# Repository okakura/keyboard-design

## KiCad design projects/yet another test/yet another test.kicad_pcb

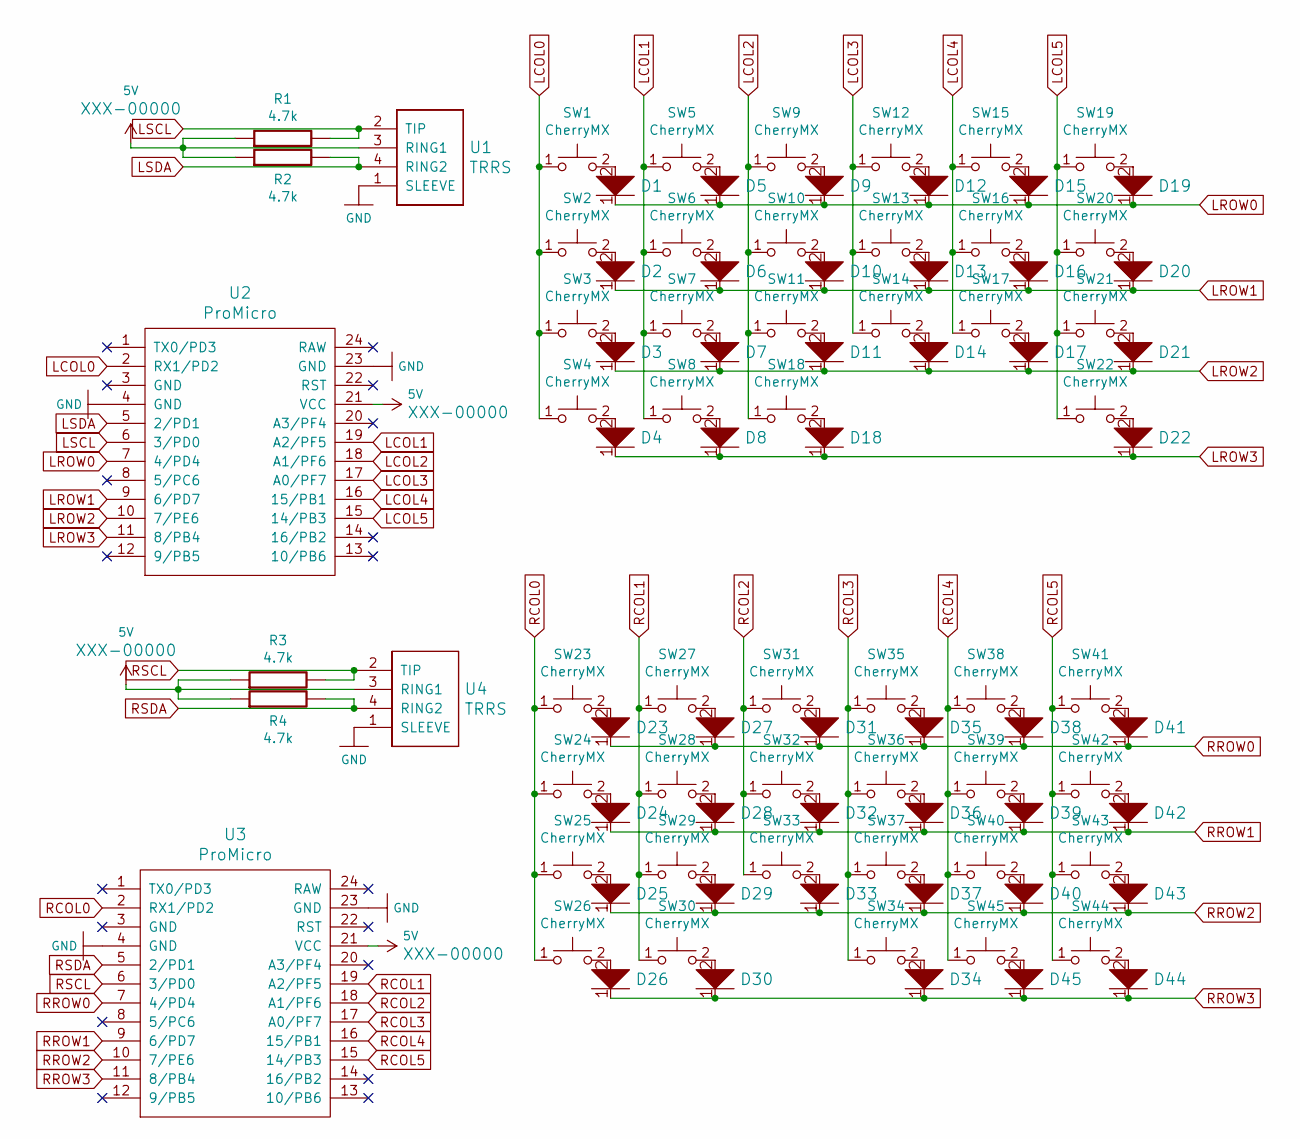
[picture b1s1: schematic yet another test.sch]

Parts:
D1, D2, D3, D4, D5, D6, D7, D8, D9, D10, D11, D12, D13, D14, D15, D16, D17, D18, D19, D20, D21, D22, D23, D24, D25, D26, D27, D28, D29, D30, D31, D32, D33, D34, D35, D36, D37, D38, D39, D40, D41, D42, D43, D44, D45: D; Diode
R1, R2, R3, R4: 4.7k; Resistor
SW1, SW5, SW6, SW7, SW9, SW10, SW11, SW12, SW13, SW14, SW15, SW16, SW17, SW19, SW20, SW21, SW23, SW24, SW25, SW27, SW28, SW29, SW31, SW32, SW33, SW34, SW35, SW36, SW37, SW38, SW39, SW40, SW43, SW44, SW45: CherryMX; CherryMX_1.00u_PCB
SW2, SW4, SW18: CherryMX; CherryMX_1.25u_PCB
SW3, SW41: CherryMX; CherryMX_1.75u_PCB
SW8, SW30, SW42: CherryMX; CherryMX_1.50u_PCB
SW22: CherryMX; CherryMX_2.25u_PCB_StabWireBottom
SW26: CherryMX; CherryMX_2.00u_PCB_StabWireBottom
U1, U4: TRRS; TRRS-PJ-320D
U2, U3: ProMicro; ArduinoProMicro

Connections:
5V: R1.1, R2.1, R3.1, R4.1, U1.3 (RING1), U2.21 (VCC), U3.21 (VCC), U4.3 (RING1)
GND: U1.1 (SLEEVE), U2.4 (GND), U2.23 (GND), U3.4 (GND), U3.23 (GND), U4.1 (SLEEVE)
LCOL0: SW1.1, SW2.1, SW3.1, SW4.1, U2.2 (RX1/PD2)
LCOL1: SW5.1, SW6.1, SW7.1, SW8.1, U2.19 (A2/PF5)
LCOL2: SW9.1, SW10.1, SW11.1, SW18.1, U2.18 (A1/PF6)
LCOL3: SW12.1, SW13.1, SW14.1, U2.17 (A0/PF7)
LCOL4: SW15.1, SW16.1, SW17.1, U2.16 (15/PB1)
LCOL5: SW19.1, SW20.1, SW21.1, SW22.1, U2.15 (14/PB3)
LROW0: D1.1, D5.1, D9.1, D12.1, D15.1, D19.1, U2.7 (4/PD4)
LROW1: D2.1, D6.1, D10.1, D13.1, D16.1, D20.1, U2.9 (6/PD7)
LROW2: D3.1, D7.1, D11.1, D14.1, D17.1, D21.1, U2.10 (7/PE6)
LROW3: D4.1, D8.1, D18.1, D22.1, U2.11 (8/PB4)
LSCL: R1.2, U1.2 (TIP), U2.6 (3/PD0)
LSDA: R2.2, U1.4 (RING2), U2.5 (2/PD1)
unnamed: D1.2, SW1.2
unnamed: D2.2, SW2.2
unnamed: D3.2, SW3.2
unnamed: D4.2, SW4.2
unnamed: D5.2, SW5.2
unnamed: D6.2, SW6.2
unnamed: D7.2, SW7.2
unnamed: D8.2, SW8.2
unnamed: D9.2, SW9.2
unnamed: D10.2, SW10.2
unnamed: D11.2, SW11.2
unnamed: D12.2, SW12.2
unnamed: D13.2, SW13.2
unnamed: D14.2, SW14.2
unnamed: D15.2, SW15.2
unnamed: D16.2, SW16.2
unnamed: D17.2, SW17.2
unnamed: D18.2, SW18.2
unnamed: D19.2, SW19.2
unnamed: D20.2, SW20.2
unnamed: D21.2, SW21.2
unnamed: D22.2, SW22.2
unnamed: D23.2, SW23.2
unnamed: D24.2, SW24.2
unnamed: D25.2, SW25.2
unnamed: D26.2, SW26.2
unnamed: D27.2, SW27.2
unnamed: D28.2, SW28.2
unnamed: D29.2, SW29.2
unnamed: D30.2, SW30.2
unnamed: D31.2, SW31.2
unnamed: D32.2, SW32.2
unnamed: D33.2, SW33.2
unnamed: D34.2, SW34.2
unnamed: D35.2, SW35.2
unnamed: D36.2, SW36.2
unnamed: D37.2, SW37.2
unnamed: D38.2, SW38.2
unnamed: D39.2, SW39.2
unnamed: D40.2, SW40.2
unnamed: D41.2, SW41.2
unnamed: D42.2, SW42.2
unnamed: D43.2, SW43.2
unnamed: D44.2, SW44.2
unnamed: D45.2, SW45.2
RCOL0: SW23.1, SW24.1, SW25.1, SW26.1, U3.2 (RX1/PD2)
RCOL1: SW27.1, SW28.1, SW29.1, SW30.1, U3.19 (A2/PF5)
RCOL2: SW31.1, SW32.1, SW33.1, U3.18 (A1/PF6)
RCOL3: SW34.1, SW35.1, SW36.1, SW37.1, U3.17 (A0/PF7)
RCOL4: SW38.1, SW39.1, SW40.1, SW45.1, U3.16 (15/PB1)
RCOL5: SW41.1, SW42.1, SW43.1, SW44.1, U3.15 (14/PB3)
RROW0: D23.1, D27.1, D31.1, D35.1, D38.1, D41.1, U3.7 (4/PD4)
RROW1: D24.1, D28.1, D32.1, D36.1, D39.1, D42.1, U3.9 (6/PD7)
RROW2: D25.1, D29.1, D33.1, D37.1, D40.1, D43.1, U3.10 (7/PE6)
RROW3: D26.1, D30.1, D34.1, D44.1, D45.1, U3.11 (8/PB4)
RSCL: R3.2, U3.6 (3/PD0), U4.2 (TIP)
RSDA: R4.2, U3.5 (2/PD1), U4.4 (RING2)

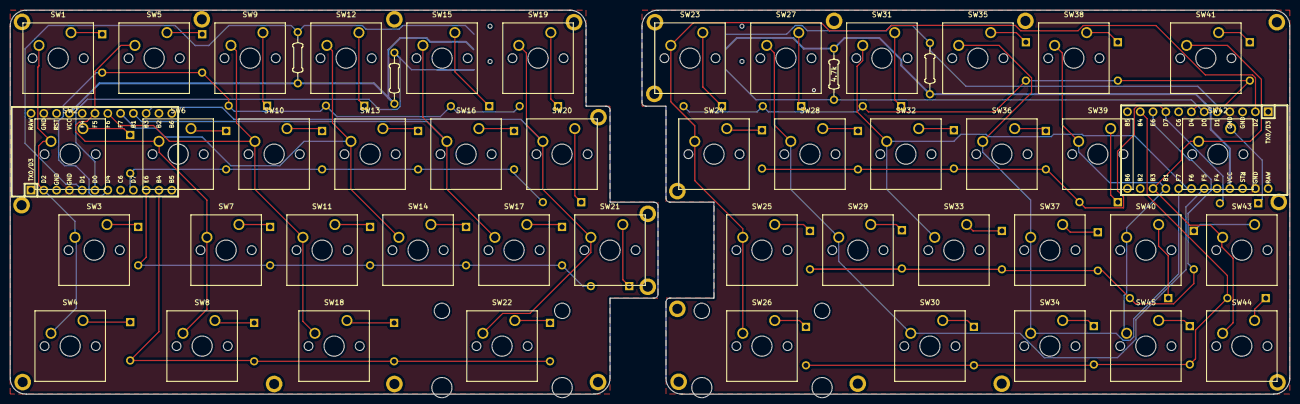
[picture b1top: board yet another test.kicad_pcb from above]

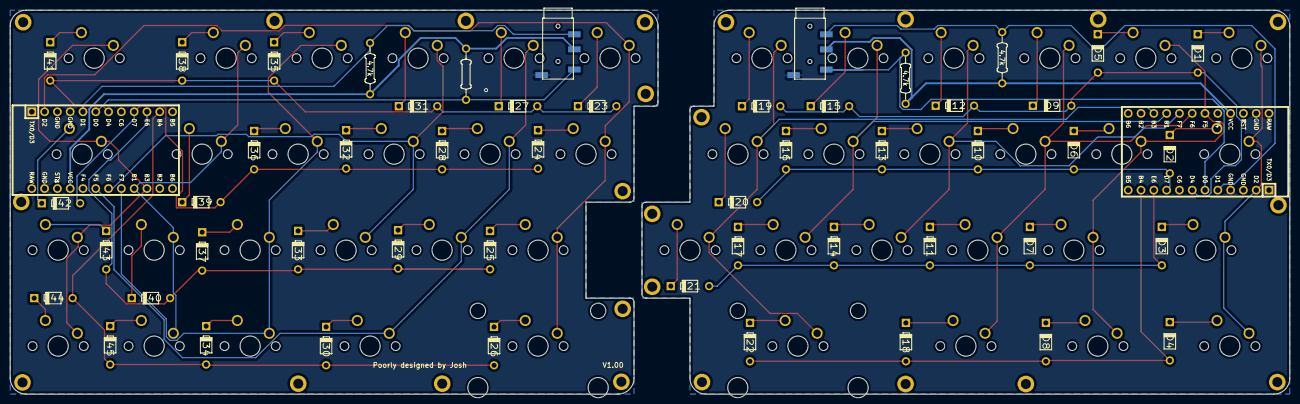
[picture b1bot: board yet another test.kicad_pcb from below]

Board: 2 copper layers, 254.0 x 76.2 mm, 121 parts (50 on the bottom side), 71 nets.

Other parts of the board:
>NAME: >VALUE; 1X01_2MM
>NAME#2, >NAME#3, >NAME#4, >NAME#5, >NAME#6, >NAME#7, >NAME#8, >NAME#9, >NAME#10, >NAME#11, >NAME#12, >NAME#13, >NAME#14, >NAME#15, >NAME#16, >NAME#17, >NAME#18, >NAME#19, >NAME#20, >NAME#21, >NAME#22, >NAME#23: >VALUE; 1X01_2MM

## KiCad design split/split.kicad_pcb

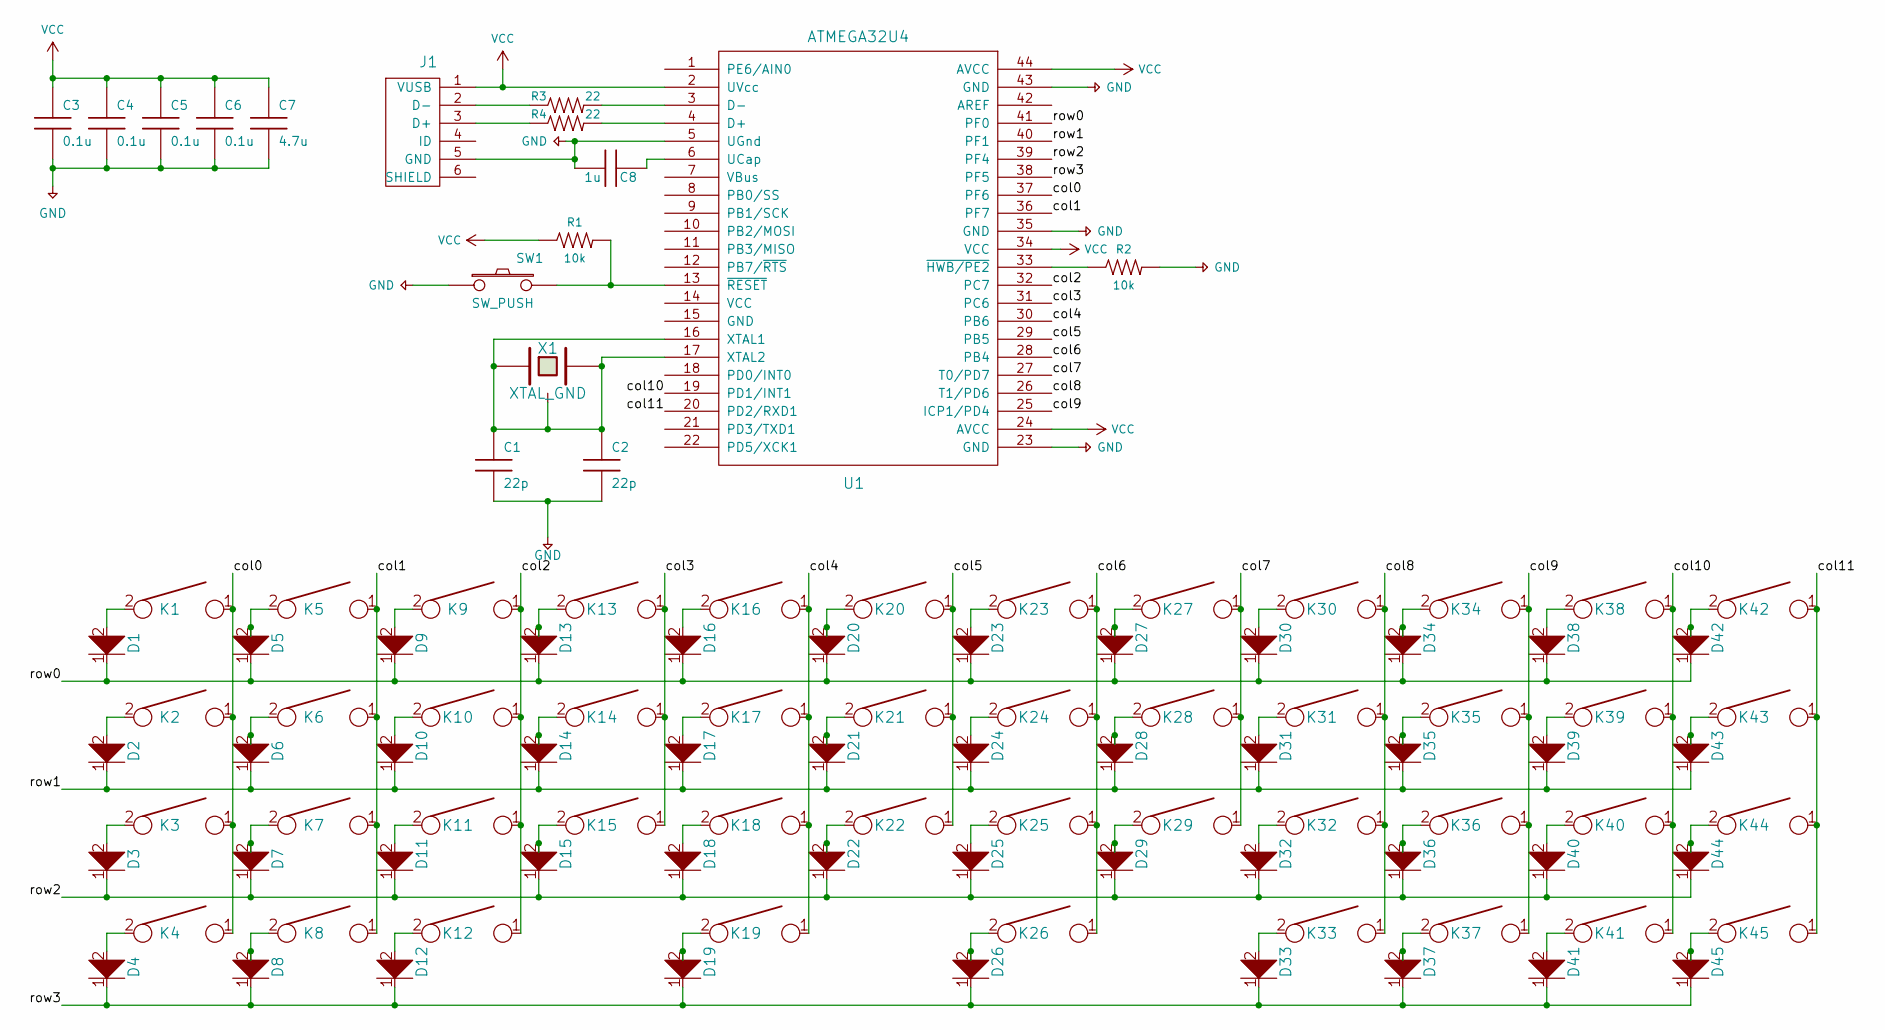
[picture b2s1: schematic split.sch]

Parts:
C1, C2: 22p; 0805
C3, C4, C5, C6: 0.1u; 0805
C7: 4.7u; 0805
C8: 1u; 0805
D1, D2, D3, D4, D5, D6, D7, D8, D9, D10, D11, D12, D13, D14, D15, D16, D17, D18, D19, D20, D21, D22, D23, D24, D25, D26, D27, D28, D29, D30, D31, D32, D33, D34, D35, D36, D37, D38, D39, D40, D41, D42, D43, D44, D45: D; D_SOD123_axial
J1: USB_mini_micro_B; USB_miniB_hirose_5S8
K1, K5, K6, K7, K9, K10, K11, K13, K14, K15, K16, K17, K18, K20, K21, K22, K23, K24, K25, K27, K28, K29, K30, K31, K32, K34, K35, K36, K37, K38, K39, K40, K41, K44, K45: KEYSW; MX-1U-NoLED
K2, K4, K12: KEYSW; MX-1.25U-NoLED
K3, K42: KEYSW; MX-1.75U-NoLED
K8, K33, K43: KEYSW; MX-1.5U-NoLED
K19: KEYSW; MX-2.25U-NoLED
K26: KEYSW; MX-2U-NoLED
R1, R2: 10k; 0805
R3, R4: 22; 0805
SW1: SW_PUSH; SW_SPST_TL3342
U1: ATMEGA32U4; TQFP-44_10x10mm_P0.8mm
X1: XTAL_GND; Crystal_SMD_3225-4Pin_3.2x2.5mm

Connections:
+5V: C1.2, C2.2, C3.2, C4.2, C5.2, C6.2, C7.2, C8.1, J1.5 (GND), R2.2, SW1.1, U1.5 (UGnd), U1.23 (GND), U1.35 (GND), U1.43 (GND)
/col0: K1.1, K2.1, K3.1, K4.1, U1.37 (PF6)
/col1: K5.1, K6.1, K7.1, K8.1, U1.36 (PF7)
/col2: K9.1, K10.1, K11.1, K12.1, U1.32 (PC7)
/col3: K13.1, K14.1, K15.1, U1.31 (PC6)
/col4: K16.1, K17.1, K18.1, K19.1, U1.30 (PB6)
/col5: K20.1, K21.1, K22.1, U1.29 (PB5)
/col6: K23.1, K24.1, K25.1, K26.1, U1.28 (PB4)
/col7: K27.1, K28.1, K29.1, U1.27 (T0/PD7)
/col8: K30.1, K31.1, K32.1, K33.1, U1.26 (T1/PD6)
/col9: K34.1, K35.1, K36.1, K37.1, U1.25 (ICP1/PD4)
/col10: K38.1, K39.1, K40.1, K41.1, U1.19 (PD1/INT1)
/col11: K42.1, K43.1, K44.1, K45.1, U1.20 (PD2/RXD1)
/row0: D1.1, D5.1, D9.1, D13.1, D16.1, D20.1, D23.1, D27.1, D30.1, D34.1, D38.1, D42.1, U1.41 (PF0)
/row1: D2.1, D6.1, D10.1, D14.1, D17.1, D21.1, D24.1, D28.1, D31.1, D35.1, D39.1, D43.1, U1.40 (PF1)
/row2: D3.1, D7.1, D11.1, D15.1, D18.1, D22.1, D25.1, D29.1, D32.1, D36.1, D40.1, D44.1, U1.39 (PF4)
/row3: D4.1, D8.1, D12.1, D19.1, D26.1, D33.1, D37.1, D41.1, D45.1, U1.38 (PF5)
unnamed: C1.1, C2.1, U1.16 (XTAL1), U1.17 (XTAL2), X1.1, X1.2, X1.3
unnamed: C8.2, U1.6 (UCap)
unnamed: D1.2, K1.2
unnamed: D2.2, K2.2
unnamed: D3.2, K3.2
unnamed: D4.2, K4.2
unnamed: D5.2, K5.2
unnamed: D6.2, K6.2
unnamed: D7.2, K7.2
unnamed: D8.2, K8.2
unnamed: D9.2, K9.2
unnamed: D10.2, K10.2
unnamed: D11.2, K11.2
unnamed: D12.2, K12.2
unnamed: D13.2, K13.2
unnamed: D14.2, K14.2
unnamed: D15.2, K15.2
unnamed: D16.2, K16.2
unnamed: D17.2, K17.2
unnamed: D18.2, K18.2
unnamed: D19.2, K19.2
unnamed: D20.2, K20.2
unnamed: D21.2, K21.2
unnamed: D22.2, K22.2
unnamed: D23.2, K23.2
unnamed: D24.2, K24.2
unnamed: D25.2, K25.2
unnamed: D26.2, K26.2
unnamed: D27.2, K27.2
unnamed: D28.2, K28.2
unnamed: D29.2, K29.2
unnamed: D30.2, K30.2
unnamed: D31.2, K31.2
unnamed: D32.2, K32.2
unnamed: D33.2, K33.2
unnamed: D34.2, K34.2
unnamed: D35.2, K35.2
unnamed: D36.2, K36.2
unnamed: D37.2, K37.2
unnamed: D38.2, K38.2
unnamed: D39.2, K39.2
unnamed: D40.2, K40.2
unnamed: D41.2, K41.2
unnamed: D42.2, K42.2
unnamed: D43.2, K43.2
unnamed: D44.2, K44.2
unnamed: D45.2, K45.2
unnamed: J1.2 (D-), R3.1
unnamed: J1.3 (D+), R4.1
unnamed: R1.2, SW1.2, U1.13 (~RESET)
unnamed: R2.1, U1.33 (~HWB/PE2)
unnamed: R3.2, U1.3 (D-)
unnamed: R4.2, U1.4 (D+)
VCC: C3.1, C4.1, C5.1, C6.1, C7.1, J1.1 (VUSB), R1.1, U1.2 (UVcc), U1.24 (AVCC), U1.34 (VCC), U1.44 (AVCC)

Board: 2 copper layers, 106 parts (61 on the bottom side), 71 nets, no tracks yet.

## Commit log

2021-07-09 first design folder
2021-07-09 adding submodules
2021-07-09 adding more submodules
2021-07-09 initial layout
2021-07-09 init pcb layout
2021-07-09 init design
2021-07-11 starting over
2021-07-12 version 1 done
